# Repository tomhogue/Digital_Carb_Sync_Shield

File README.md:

Digital Carb Sync Shield
========================

For the latest version and organization visit https://digitalcarbsync.com

Motorcycle carburetor synchronization. Analog sensors. LCD display. Easy to build. Wiki.

This repository is for the Digital Carb Sync Shield project. The shield is designed for the Arduino UNO R3
and other compatible boards.

The software is licensed under the MIT model.
The hardware is licensed using Open Hardware License.

The shield reads up to 6 vacuum pressure sensors on A0-5 and displays running peaks.

There is a calibration step to average the analog inputs. This is to compensate for build quality issues.

###Bill of Materials#

Some PCB boards may be available to GitHub collaborators.

Partial BOM sourced at Digi-Key. Shop around.

###More information and history at#

http://www.venturerider.org/forum/showthread.php?90191-New-digital-carb-sync-board

and its evolution from old auto parts

http://www.venturerider.org/forum/showthread.php?73158-Built-a-digital-carb-sync

and for Honda Valkyrie riders

http://www.valkyrieforum.com/bbs/index.php/topic,73795.0.html
http://www.valkyrieforum.com/bbs/index.php/topic,74909.0.html

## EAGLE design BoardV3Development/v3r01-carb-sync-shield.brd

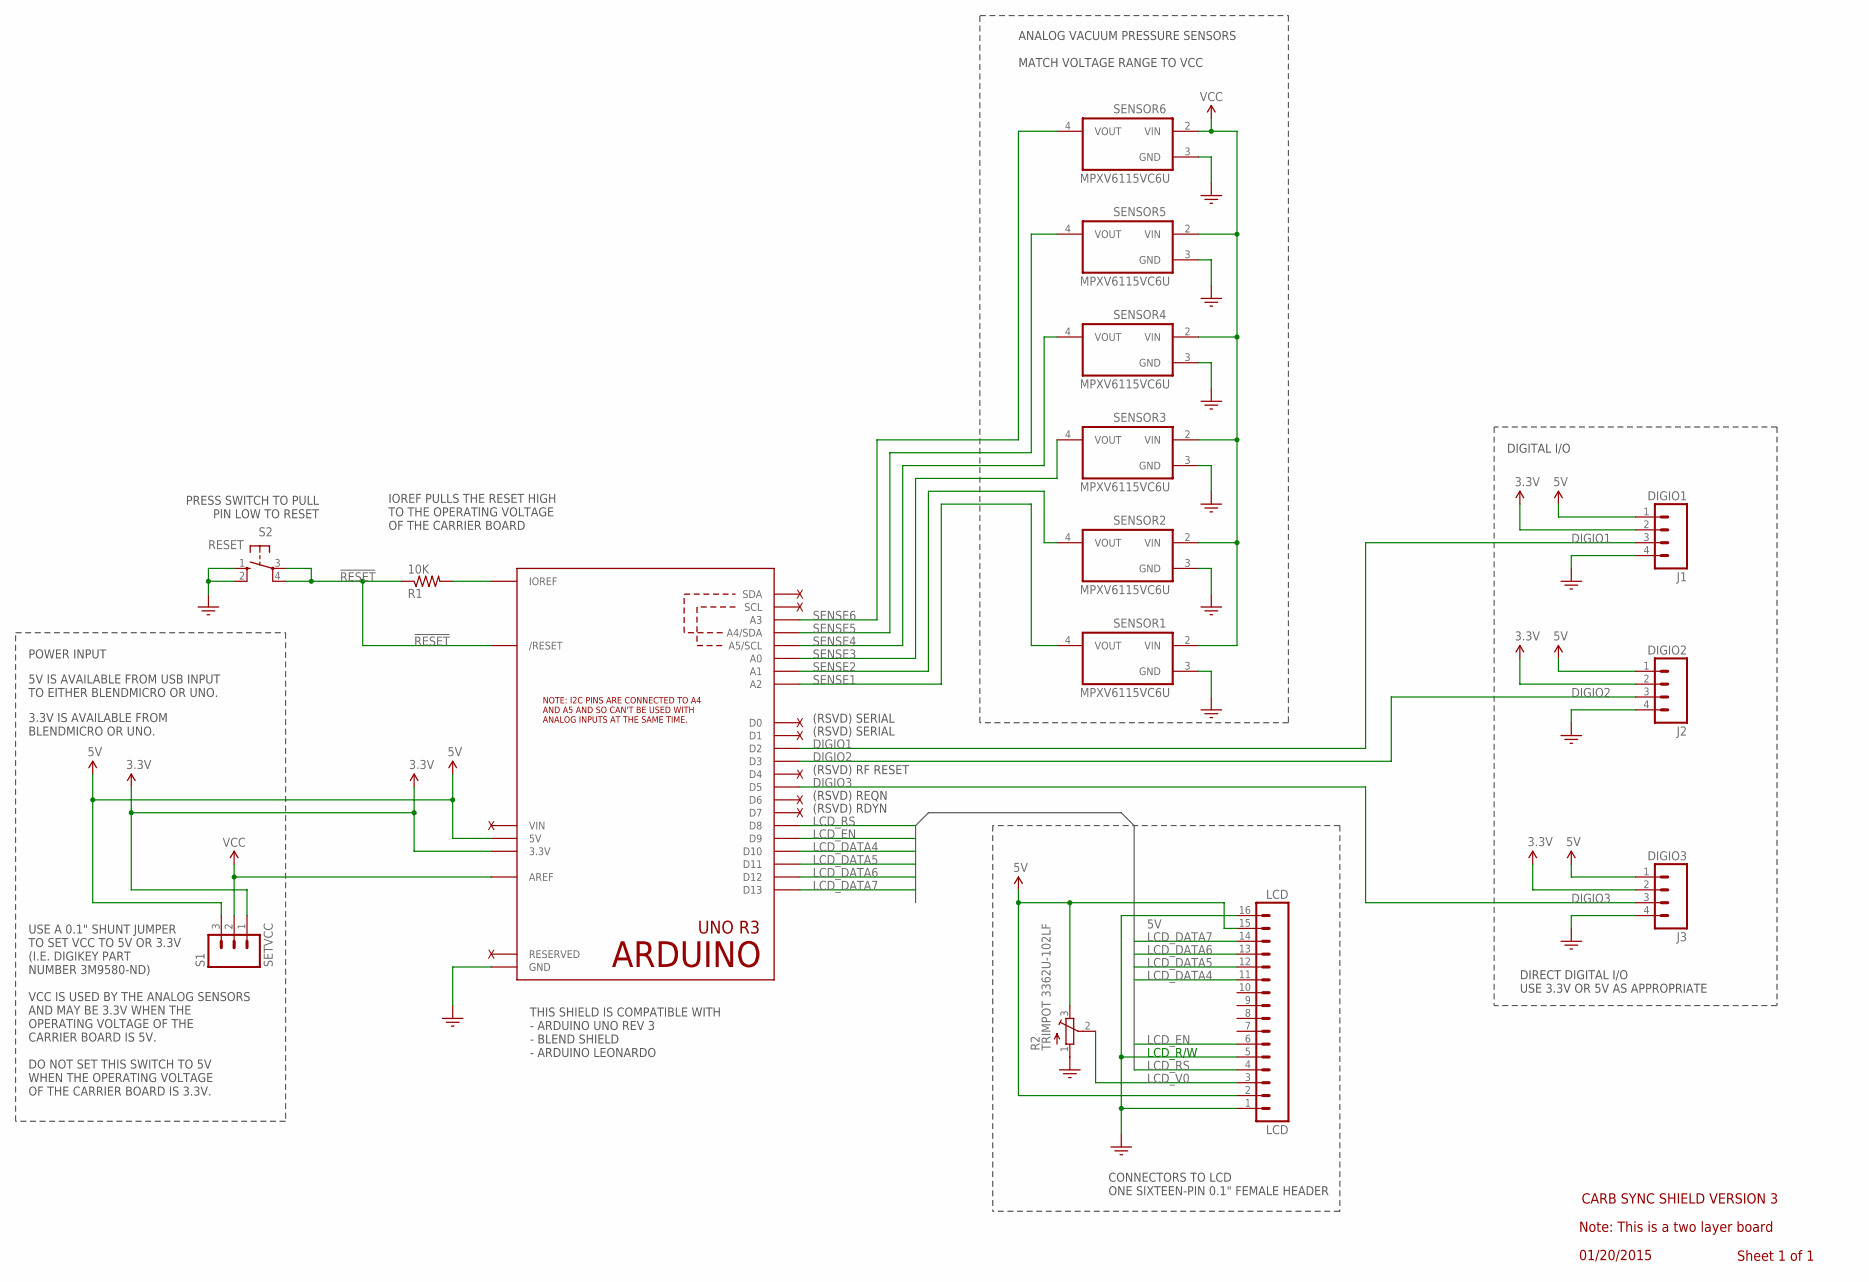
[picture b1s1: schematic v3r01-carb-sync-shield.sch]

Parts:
J1: DIGIO1; 1X04_LONGPADS
J2: DIGIO2; 1X04_LONGPADS
J3: DIGIO3; 1X04_LONGPADS
LCD: LCD; CARBSYNCSHIELD_LCD
R1: 10K; 0411/12
R2: TRIMPOT 3362U-102LF; TRIM-3386
S1: SETVCC; 1X03_LONGPADS
S2: RESET; B3F-10XX
SENSOR1, SENSOR2, SENSOR3, SENSOR4, SENSOR5, SENSOR6: MPXV6115VC6U; MPXV6115VC6U/T1-CASE482A
U$13: ARDUINO-UNO-R3; ARDUINO-UNO-R3-HOLES-NODIM

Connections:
3.3V: J1.2, J2.2, J3.2, S1.1, U$13.3V (3.3V)
5V: J1.1, J2.1, J3.1, LCD.2, LCD.15, R2.3 (E), S1.3, U$13.5V
!RESET: R1.1, S2.3, S2.4 (P1), U$13.RESET (/RESET)
DIGIO1: J1.3, U$13.D2
DIGIO2: J2.3, U$13.D3
DIGIO3: J3.3, U$13.D5
GND: J1.4, J2.4, J3.4, LCD.1, LCD.5, LCD.16, R2.1 (A), S2.1 (S), S2.2 (S1), SENSOR1.3 (GND), SENSOR2.3 (GND), SENSOR3.3 (GND), SENSOR4.3 (GND), SENSOR5.3 (GND), SENSOR6.3 (GND), U$13.GND, U$13.GND1 (GND), U$13.GND2 (GND)
IOREF: R1.2, U$13.IOREF
LCD_DATA4: LCD.11, U$13.D10
LCD_DATA5: LCD.12, U$13.D11
LCD_DATA6: LCD.13, U$13.D12
LCD_DATA7: LCD.14, U$13.D13
LCD_EN: LCD.6, U$13.D9
LCD_RS: LCD.4, U$13.D8
LCD_V0: LCD.3, R2.2 (S)
SENSE1: SENSOR1.4 (VOUT), U$13.A2
SENSE2: SENSOR2.4 (VOUT), U$13.A1
SENSE3: SENSOR3.4 (VOUT), U$13.A0
SENSE4: SENSOR4.4 (VOUT), U$13.A5 (A5/SCL)
SENSE5: SENSOR5.4 (VOUT), U$13.A4 (A4/SDA)
SENSE6: SENSOR6.4 (VOUT), U$13.A3
VCC: S1.2, SENSOR1.2 (VIN), SENSOR2.2 (VIN), SENSOR3.2 (VIN), SENSOR4.2 (VIN), SENSOR5.2 (VIN), SENSOR6.2 (VIN), U$13.AREF
VIN: U$13.VIN

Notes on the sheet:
ANALOG VACUUM PRESSURE SENSORS MATCH VOLTAGE RANGE TO VCC
PRESS SWITCH TO PULL PIN LOW TO RESET
CARB SYNC SHIELD VERSION 3
Sheet 1 of 1
01/20/2015
Note: This is a two layer board
CONNECTORS TO LCD ONE SIXTEEN-PIN 0.1" FEMALE HEADER
LCD_R/W
DIGITAL I/O
5V IS AVAILABLE FROM USB INPUT TO EITHER BLENDMICRO OR UNO.
3.3V IS AVAILABLE FROM BLENDMICRO OR UNO.
POWER INPUT
DIRECT DIGITAL I/O USE 3.3V OR 5V AS APPROPRIATE
THIS SHIELD IS COMPATIBLE WITH - ARDUINO UNO REV 3 - BLEND SHIELD - ARDUINO LEONARDO
(RSVD) REQN
(RSVD) RF RESET
(RSVD) RDYN
(RSVD) SERIAL
IOREF PULLS THE RESET HIGH TO THE OPERATING VOLTAGE OF THE CARRIER BOARD
USE A 0.1" SHUNT JUMPER TO SET VCC TO 5V OR 3.3V (I.E. DIGIKEY PART NUMBER 3M9580-ND) VCC IS USED BY THE ANALOG SENSORS AND MAY BE 3.3V WHEN THE OPERATING VOLTAGE OF THE CARRIER BOARD IS 5V. DO NOT SET THIS SWITCH TO 5V WHEN THE OPERATING VOLTAGE OF THE CARRIER BOARD IS 3.3V.

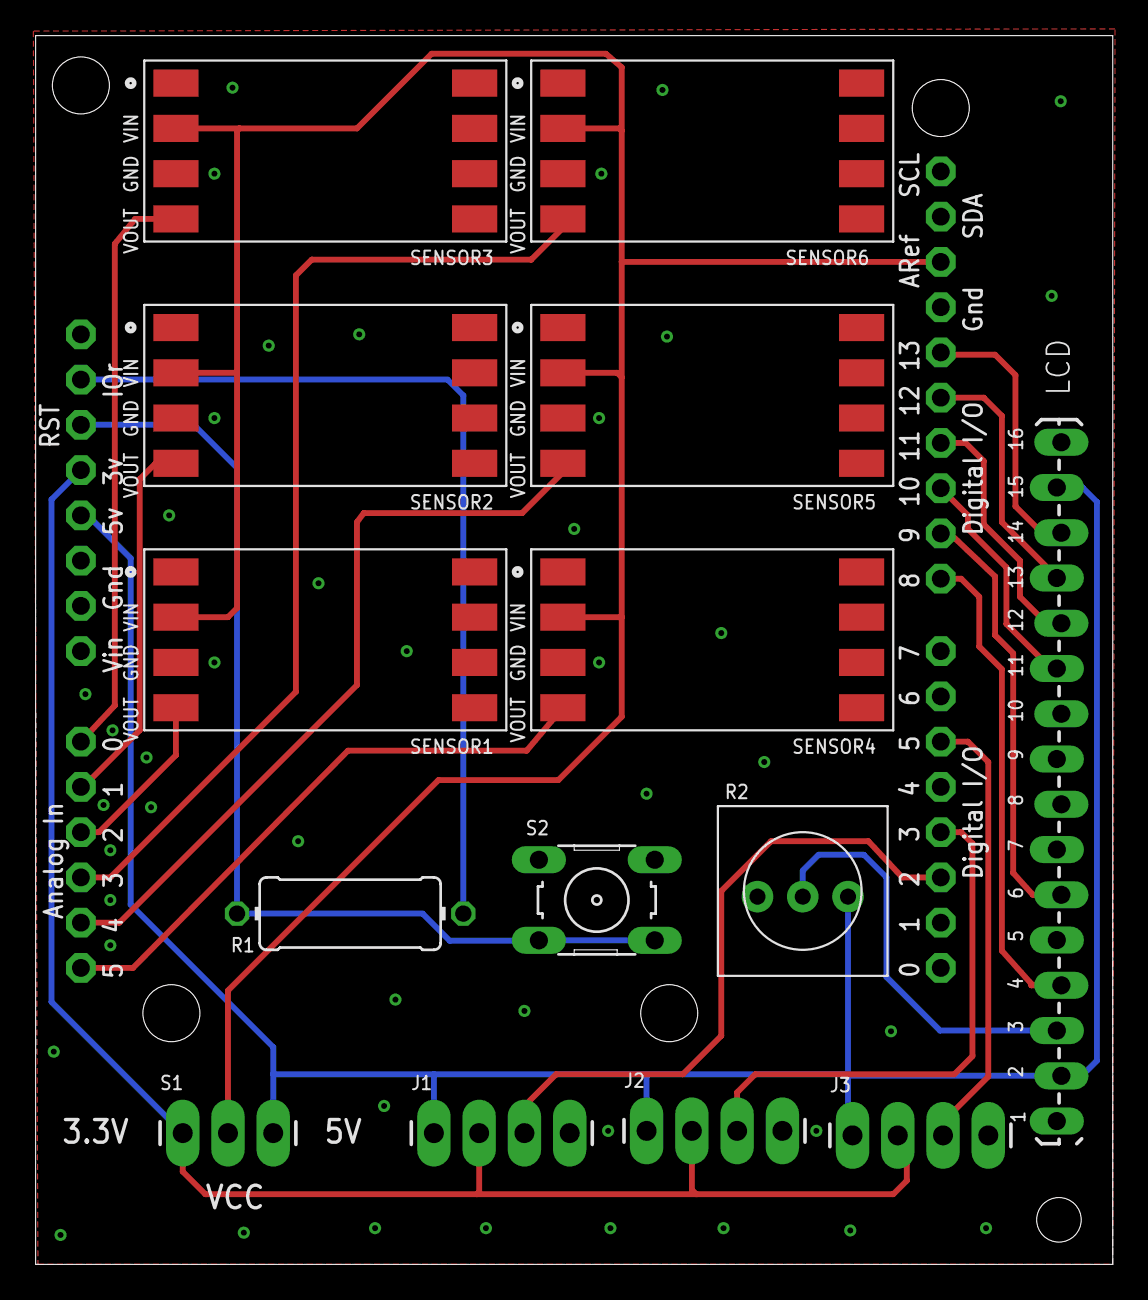
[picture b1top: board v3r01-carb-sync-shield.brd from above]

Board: 2 copper layers, 60.5 x 69.0 mm, 15 parts (0 on the bottom side), 22 nets.

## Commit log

2014-11-29 :space_invader: Added .gitattributes & .gitignore files
2014-11-30 First commit
    This is the first publication of the software for the Digital Carb Sync
    Shield software for Arduino.
2014-11-30 Create LICENSE
2014-11-30 Update LICENSE to add open hardware license
2014-11-30 add V2 board and schematic files
    The V2 board and schematic files.
2014-11-30 V2 gerber files
2014-11-30 Bill of materials
    Partial BOM sourced at Digi-Key. Shop around.
    Also requires 16x2 LCD such as this standard LCD from Adafruit. NOTE:
    This LCD comes with a header strip which reduces the need for headers on
    the BOM. It also comes with a trimmer pot the board is NOT designed for.
    https://www.adafruit.com/products/181
2015-01-17 Update BOM
    Updates to the bill of materials files
2015-01-20 Final V2 and start V3 development
    This changes closes out V2 and initiates V3
2015-01-20 change names and labels to v3
2015-01-22 Change to readme
    Remove reference to outdated LCD source
2015-01-24 version and revision labels
    add v3r01 to board and schematic files
2015-01-24 Update README.md
    Add another forum link of interest.
2015-03-08 remove old board files temp
    Remove old board files. Will post V3 soon.
2015-04-12 remove ino temp
    pulling the old version before v3
2015-04-19 replace v2
    replace v2 pending more v3 work
2015-08-18 Add CD and RPM test V02R37
    R37 includeds RPM code

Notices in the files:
BoardV3Development/v3r01-carb-sync-shield.brd:
(c) 2015 Tom Hogue
parts and their libraries:
SparkFun-Connectors: Licensing: Creative Commons ShareAlike 4.0 International - https://creativecommons.org/licenses/by-sa/4.0
